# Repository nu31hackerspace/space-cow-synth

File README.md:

# space-cow-synth
Space Cow Synth

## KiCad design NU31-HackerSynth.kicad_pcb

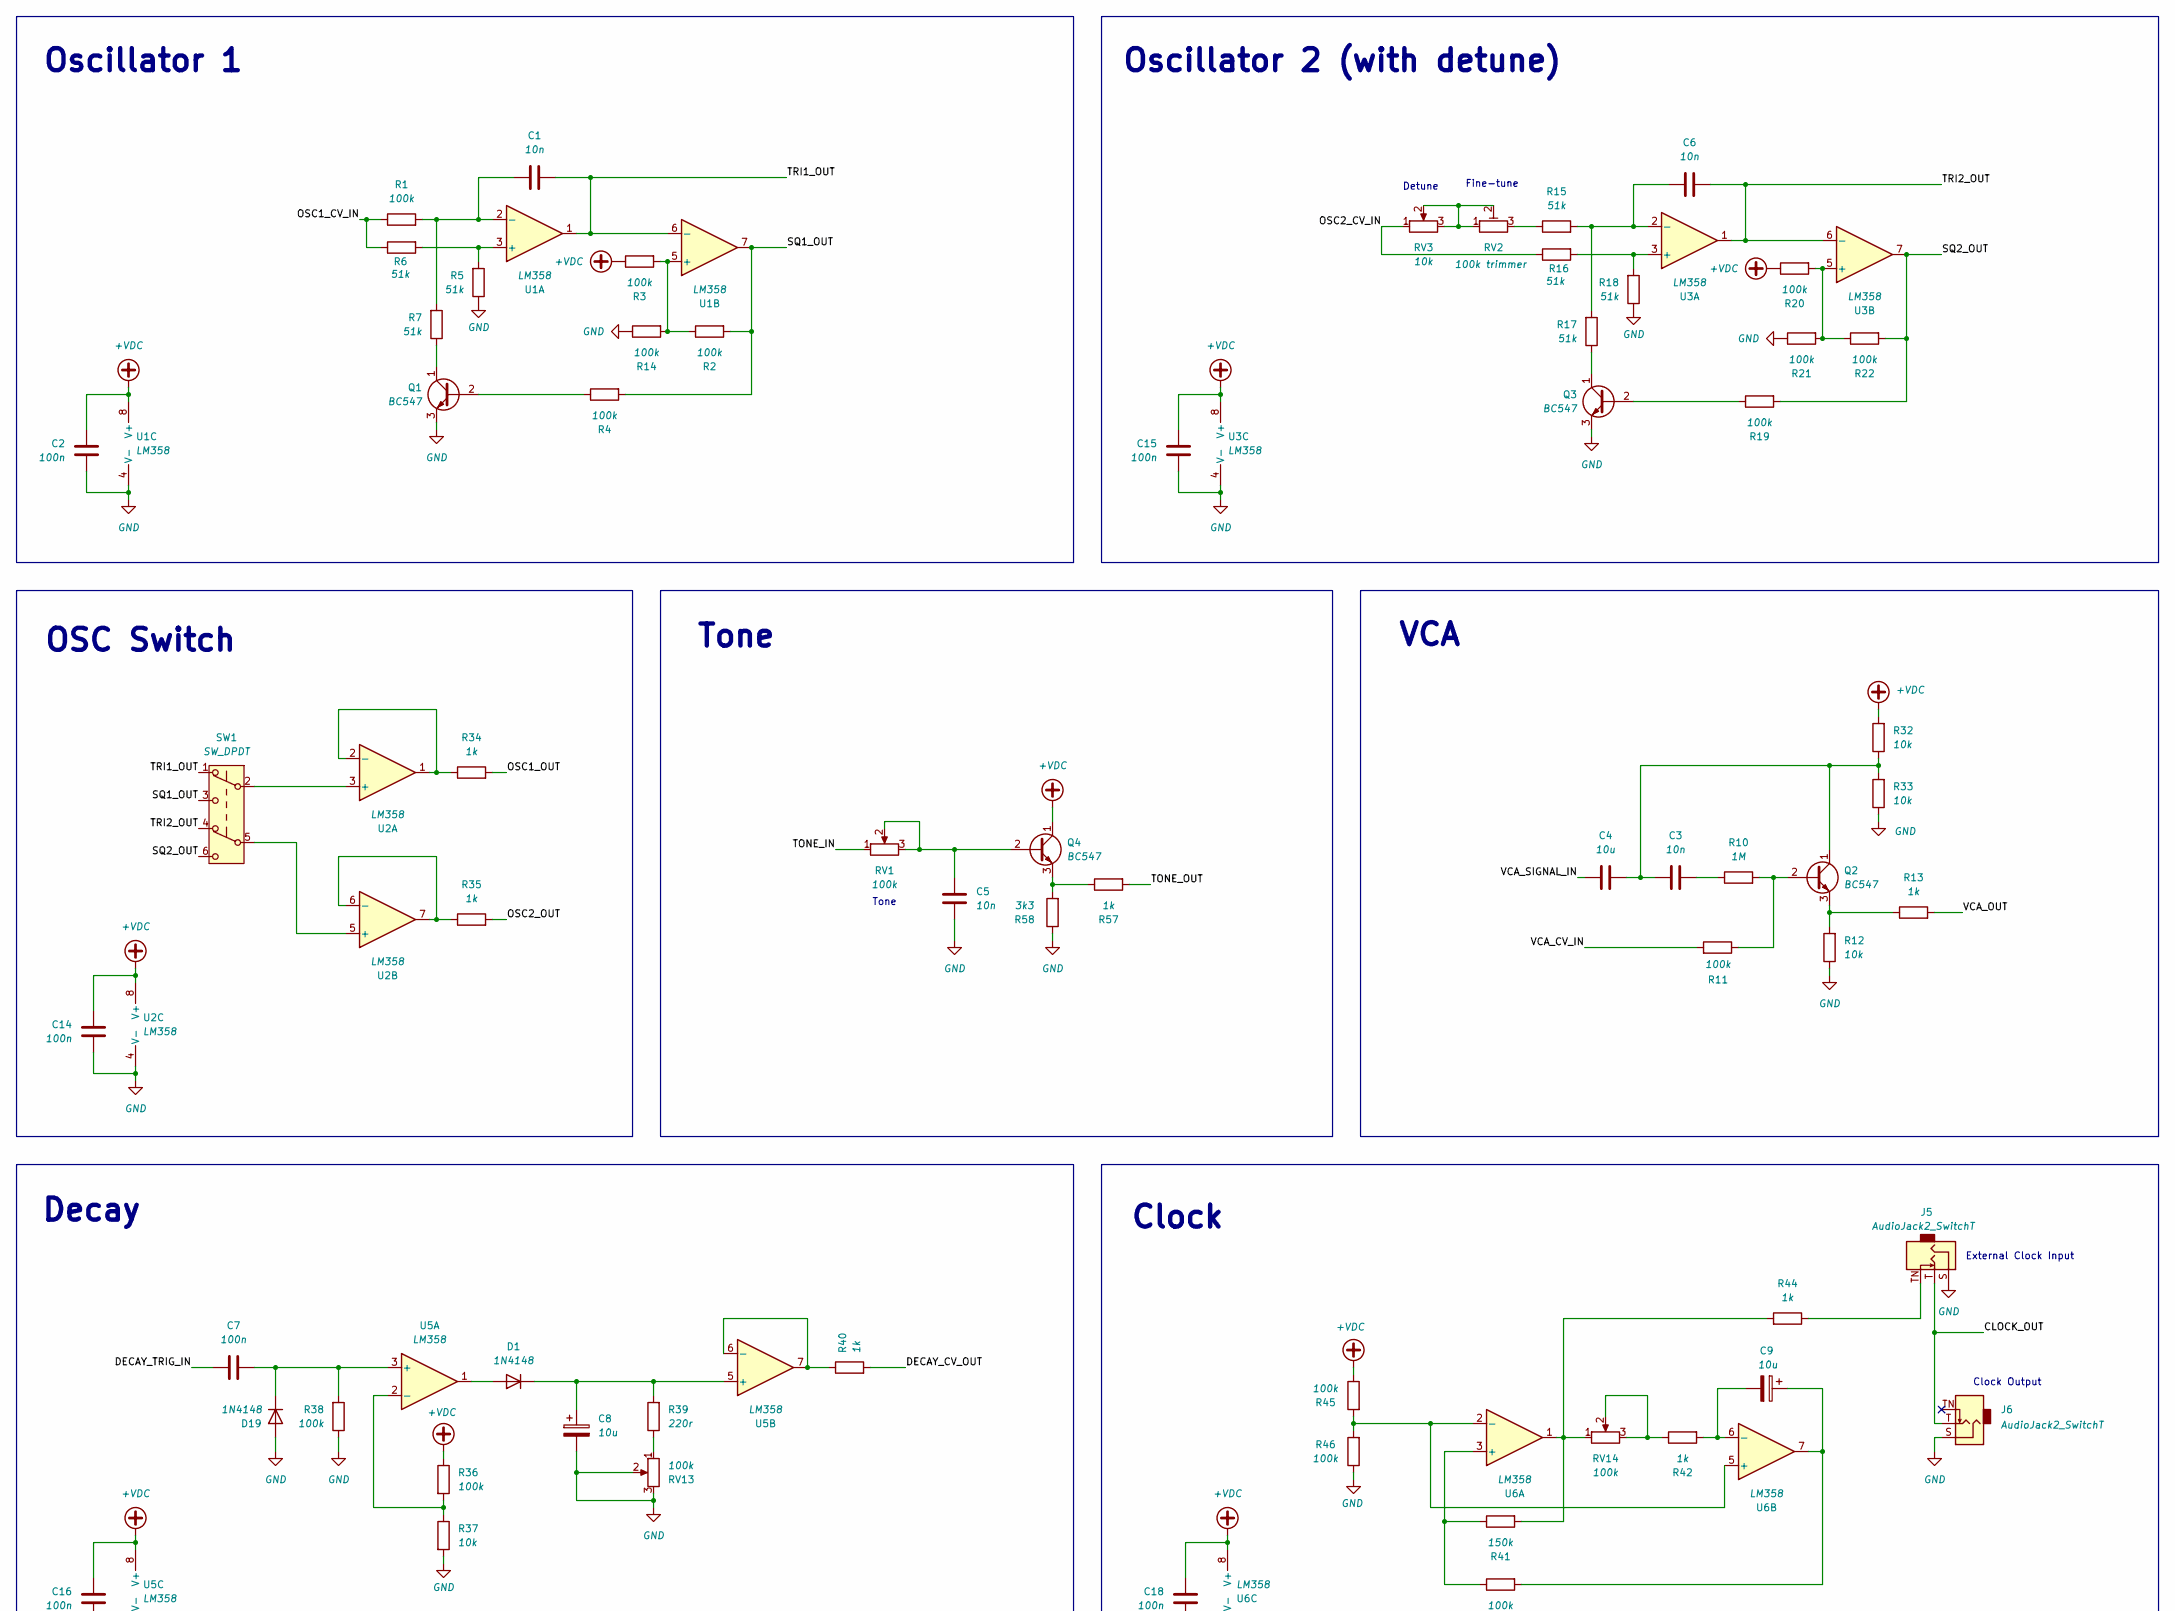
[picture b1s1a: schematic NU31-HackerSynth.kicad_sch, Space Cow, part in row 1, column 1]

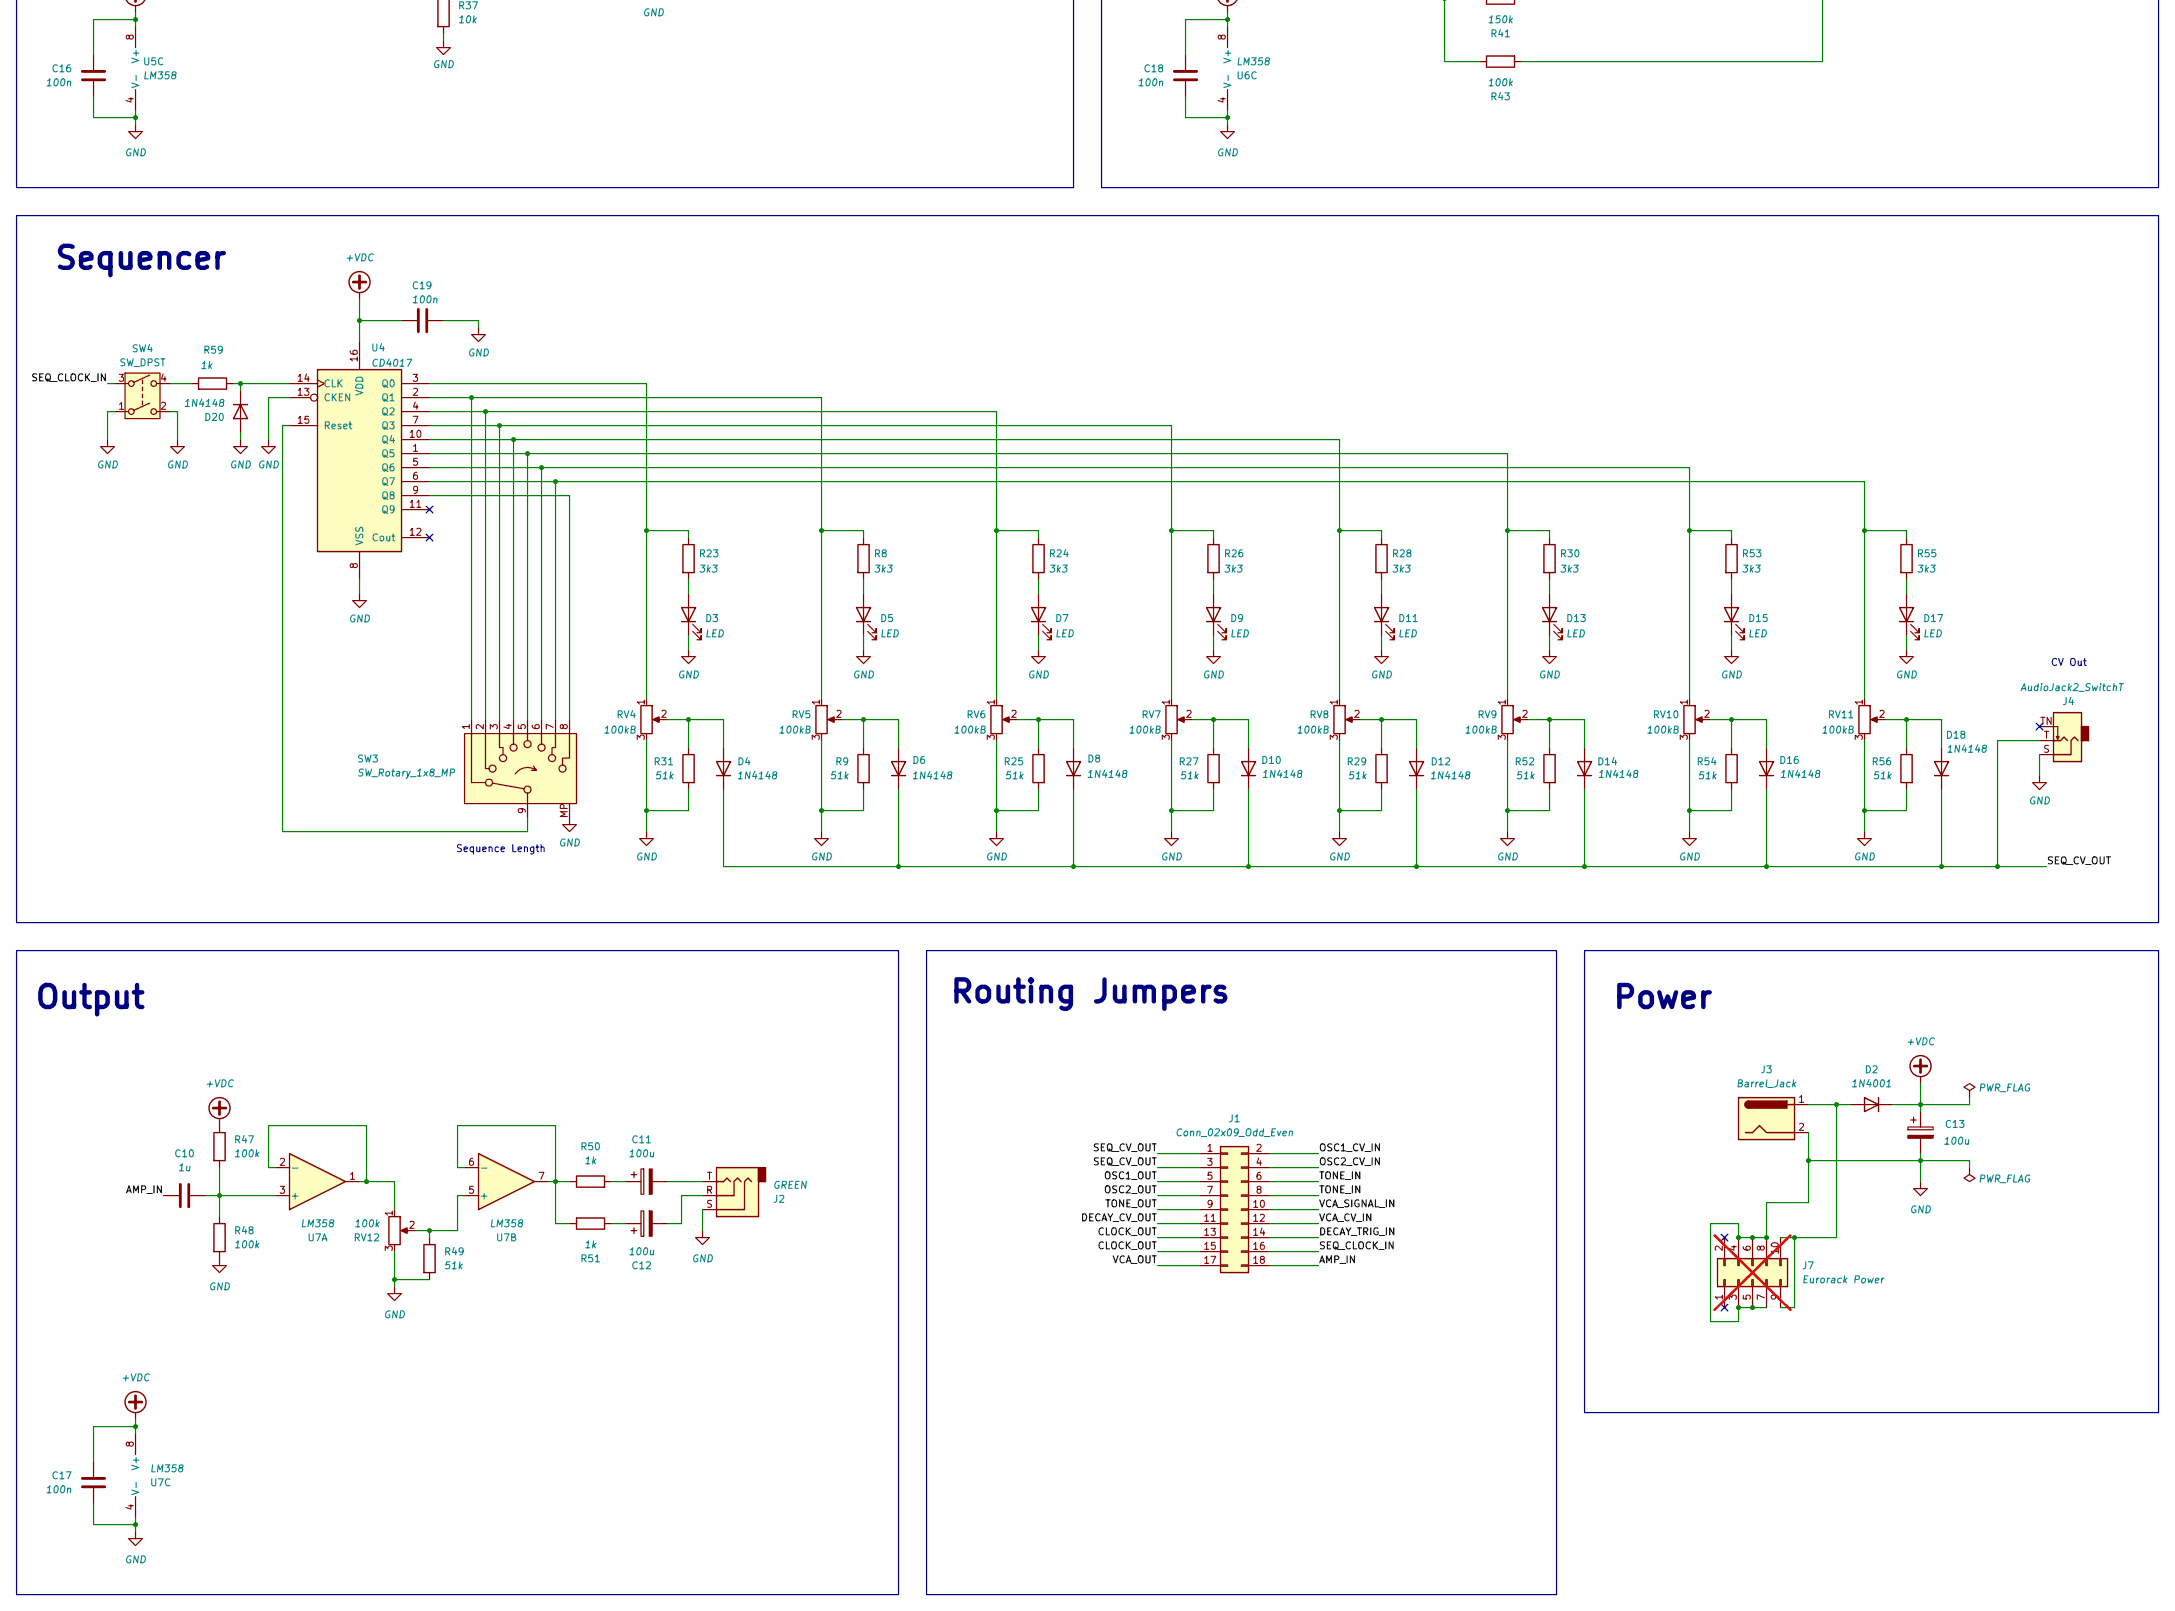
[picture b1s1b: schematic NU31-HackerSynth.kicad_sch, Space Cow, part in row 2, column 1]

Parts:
C1, C3, C5, C6: 10n; C_Disc_D5.1mm_W3.2mm_P5.00mm
C2, C7, C14, C15, C16, C17, C18, C19: 100n; C_Disc_D5.1mm_W3.2mm_P5.00mm
C4: 10u; C_Disc_D5.1mm_W3.2mm_P5.00mm
C8, C9: 10u; CP_Radial_D5.0mm_P2.50mm
C10: 1u; C_Disc_D5.1mm_W3.2mm_P5.00mm
C11, C12, C13: 100u; CP_Radial_D5.0mm_P2.50mm
D1, D4, D6, D8, D10, D12, D14, D16, D18, D19, D20: 1N4148; D_A-405_P7.62mm_Horizontal
D2: 1N4001; D_A-405_P10.16mm_Horizontal
D3, D5, D7, D9, D11, D13, D15, D17: LED; LED_D3.0mm
J1: Conn_02x09_Odd_Even; PinHeader_2x09_P2.54mm_Vertical
J2: GREEN; Jack_3.5mm_QingPu_WQP-PJ366ST_Vertical
J3: Barrel_Jack; BarrelJack_Wuerth_6941xx301002
J4, J5, J6: AudioJack2_SwitchT; Jack_3.5mm_QingPu_WQP-PJ301M-12_Vertical
J7: Eurorack Power; PinSocket_2x05_P2.54mm_Vertical; not fitted
Q1, Q2, Q3, Q4: BC547; TO-92L_Inline_Wide
R1, R2, R3, R4, R11, R14, R19, R20, R21, R22, R36, R38, R43, R45, R46, R47, R48: 100k; R_Axial_DIN0207_L6.3mm_D2.5mm_P10.16mm_Horizontal
R5, R6, R7, R9, R15, R16, R17, R18, R25, R27, R29, R31, R49, R52, R54, R56: 51k; R_Axial_DIN0207_L6.3mm_D2.5mm_P10.16mm_Horizontal
R8, R23, R24, R26, R28, R30, R53, R55, R58: 3k3; R_Axial_DIN0207_L6.3mm_D2.5mm_P10.16mm_Horizontal
R10: 1M; R_Axial_DIN0207_L6.3mm_D2.5mm_P10.16mm_Horizontal
R12, R32, R33, R37: 10k; R_Axial_DIN0207_L6.3mm_D2.5mm_P10.16mm_Horizontal
R13, R34, R35, R40, R42, R44, R50, R51, R57, R59: 1k; R_Axial_DIN0207_L6.3mm_D2.5mm_P10.16mm_Horizontal
R39: 220r; R_Axial_DIN0207_L6.3mm_D2.5mm_P10.16mm_Horizontal
R41: 150k; R_Axial_DIN0207_L6.3mm_D2.5mm_P10.16mm_Horizontal
RV1, RV12, RV13, RV14: 100k; Potentiometer_Alpha_RD901F-40-00D_Single_Vertical
RV2: 100k trimmer; Potentiometer_Bourns_3299P_Horizontal
RV3: 10k; Potentiometer_Alpha_RD901F-40-00D_Single_Vertical
RV4, RV5, RV6, RV7, RV8, RV9, RV10, RV11: 100kB; 40mm Fader Potentiometer (double)
SW1: SW_DPDT; DPDT-subminiature-toggle
SW3: SW_Rotary_1x8_MP; 8-way Rotary Switch
SW4: SW_DPST; 8x8_DPDT_Push_Button
U1, U2, U3, U5, U6, U7: LM358; DIP-8_W7.62mm_Socket
U4: CD4017; DIP-16_W7.62mm_Socket

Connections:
+VDC: C2.1, C13.1, C14.1, C15.1, C16.1, C17.1, C18.1, C19.2, D2.1 (K), Q4.1 (C), R3.1, R20.1, R32.2, R36.1, R45.1, R47.1, U1.8 (V+), U2.8 (V+), U3.8 (V+), U4.16 (VDD), U5.8 (V+), U6.8 (V+), U7.8 (V+)
/AMP_IN: C10.1, J1.18
/CLOCK_OUT: J1.13, J1.15, J5.T, J6.T
/DECAY_CV_OUT: J1.11, R40.2
/DECAY_TRIG_IN: C7.1, J1.14
/OSC1_CV_IN: J1.2, R1.1, R6.1
/OSC1_OUT: J1.5, R34.2
/OSC2_CV_IN: J1.4, R16.1, RV3.1
/OSC2_OUT: J1.7, R35.2
/SEQ_CLOCK_IN: J1.16, SW4.3
/SEQ_CV_OUT: D4.1 (K), D6.1 (K), D8.1 (K), D10.1 (K), D12.1 (K), D14.1 (K), D16.1 (K), D18.1 (K), J1.1, J1.3, J4.T
/SQ1_OUT: R2.2, R4.2, SW1.3 (C), U1.7
/SQ2_OUT: R19.2, R22.2, SW1.6 (C), U3.7
/TONE_IN: J1.6, J1.8, RV1.1
/TONE_OUT: J1.9, R57.2
/TRI1_OUT: C1.2, SW1.1 (A), U1.1, U1.6 (-)
/TRI2_OUT: C6.2, SW1.4 (A), U3.1, U3.6 (-)
/VCA_CV_IN: J1.12, R11.2
/VCA_OUT: J1.17, R13.2
/VCA_SIGNAL_IN: C4.1, J1.10
GND: C2.2, C5.2, C8.2, C13.2, C14.2, C15.2, C16.2, C17.2, C18.2, C19.1, D3.1 (K), D5.1 (K), D7.1 (K), D9.1 (K), D11.1 (K), D13.1 (K), D15.1 (K), D17.1 (K), D19.2 (A), D20.2 (A), J2.S, J3.2, J4.S, J5.S, J6.S, J7.3, J7.4, J7.5, J7.6, J7.7, J7.8, Q1.3 (E), Q3.3 (E), R5.1, R9.2, R12.1, R14.1, R18.1, R21.1, R25.2, R27.2, R29.2, R31.2, R33.1, R37.2, R38.1, R46.1, R48.2, R49.2, R52.2, R54.2, R56.2, R58.1, RV4.3, RV5.3, RV6.3, RV7.3, RV8.3, RV9.3, RV10.3, RV11.3, RV12.3, RV13.2, RV13.3, SW3.MP, SW4.1, SW4.2, U1.4 (V-), U2.4 (V-), U3.4 (V-), U4.8 (VSS), U4.13 (CKEN), U5.4 (V-), U6.4 (V-), U7.4 (V-)
unnamed: C3.2, R10.1
unnamed: C9.1, R43.2, U6.7
unnamed: C11.1, R50.2
unnamed: C11.2, J2.T
unnamed: C12.1, R51.1
unnamed: C12.2, J2.R
unnamed: D1.2 (A), U5.1
unnamed: C8.1, D1.1 (K), R39.2, U5.5 (+)
unnamed: D2.2 (A), J3.1, J7.9, J7.10
unnamed: D3.2 (A), R23.2
unnamed: D4.2 (A), R31.1, RV4.2
unnamed: D5.2 (A), R8.2
unnamed: D6.2 (A), R9.1, RV5.2
unnamed: D7.2 (A), R24.2
unnamed: D8.2 (A), R25.1, RV6.2
unnamed: D9.2 (A), R26.2
unnamed: D10.2 (A), R27.1, RV7.2
unnamed: D11.2 (A), R28.2
unnamed: D12.2 (A), R29.1, RV8.2
unnamed: D13.2 (A), R30.2
unnamed: D14.2 (A), R52.1, RV9.2
unnamed: D15.2 (A), R53.2
unnamed: D16.2 (A), R54.1, RV10.2
unnamed: D17.2 (A), R55.2
unnamed: D18.2 (A), R56.1, RV11.2
unnamed: C7.2, D19.1 (K), R38.2, U5.3 (+)
unnamed: D20.1 (K), R59.1, U4.14 (CLK)
unnamed: J5.TN, R44.1
unnamed: Q1.2 (B), R4.1
unnamed: Q1.1 (C), R7.1
unnamed: Q2.2 (B), R10.2, R11.1
unnamed: C3.1, C4.2, Q2.1 (C), R32.1, R33.2
unnamed: Q2.3 (E), R12.2, R13.1
unnamed: Q3.2 (B), R19.1
unnamed: Q3.1 (C), R17.1
unnamed: C5.1, Q4.2 (B), RV1.2, RV1.3
unnamed: Q4.3 (E), R57.1, R58.2
unnamed: R15.1, RV2.3
unnamed: R39.1, RV13.1
unnamed: R41.2, R44.2, RV14.1, U6.1
unnamed: R42.1, RV14.2, RV14.3
unnamed: R59.2, SW4.4
unnamed: RV2.1, RV2.2, RV3.2, RV3.3
unnamed: R5.2, R6.2, U1.3 (+)
unnamed: C1.1, R1.2, R7.2, U1.2 (-)
unnamed: R2.1, R3.2, R14.2, U1.5 (+)
unnamed: SW1.2 (B), U2.3 (+)
unnamed: R34.1, U2.1, U2.2 (-)
unnamed: SW1.5 (B), U2.5 (+)
unnamed: R35.1, U2.6 (-), U2.7
unnamed: R16.2, R18.2, U3.3 (+)
unnamed: C6.1, R15.2, R17.2, U3.2 (-)
unnamed: R20.2, R21.2, R22.1, U3.5 (+)
unnamed: R23.1, RV4.1, U4.3 (Q0)
unnamed: R8.1, RV5.1, SW3.1, U4.2 (Q1)
unnamed: R24.1, RV6.1, SW3.2, U4.4 (Q2)
unnamed: R26.1, RV7.1, SW3.3, U4.7 (Q3)
unnamed: R28.1, RV8.1, SW3.4, U4.10 (Q4)
unnamed: R30.1, RV9.1, SW3.5, U4.1 (Q5)
unnamed: R53.1, RV10.1, SW3.6, U4.5 (Q6)
unnamed: R55.1, RV11.1, SW3.7, U4.6 (Q7)
unnamed: SW3.8, U4.9 (Q8)
unnamed: SW3.9, U4.15 (Reset)
unnamed: R36.2, R37.1, U5.2 (-)
unnamed: R40.1, U5.6 (-), U5.7
unnamed: R41.1, R43.1, U6.3 (+)
unnamed: R45.2, R46.2, U6.2 (-), U6.5 (+)
unnamed: C9.2, R42.2, U6.6 (-)
unnamed: C10.2, R47.2, R48.1, U7.3 (+)
unnamed: RV12.1, U7.1, U7.2 (-)
unnamed: R49.1, RV12.2, U7.5 (+)
unnamed: R50.1, R51.2, U7.6 (-), U7.7

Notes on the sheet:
Sequencer
VCA
Oscillator 2 (with detune)
CV Out
Fine-tune
Power
Clock Output
Sequence Length
Tone
Routing Jumpers
Decay
External Clock Input
Output
Oscillator 1
OSC Switch
Detune
Clock

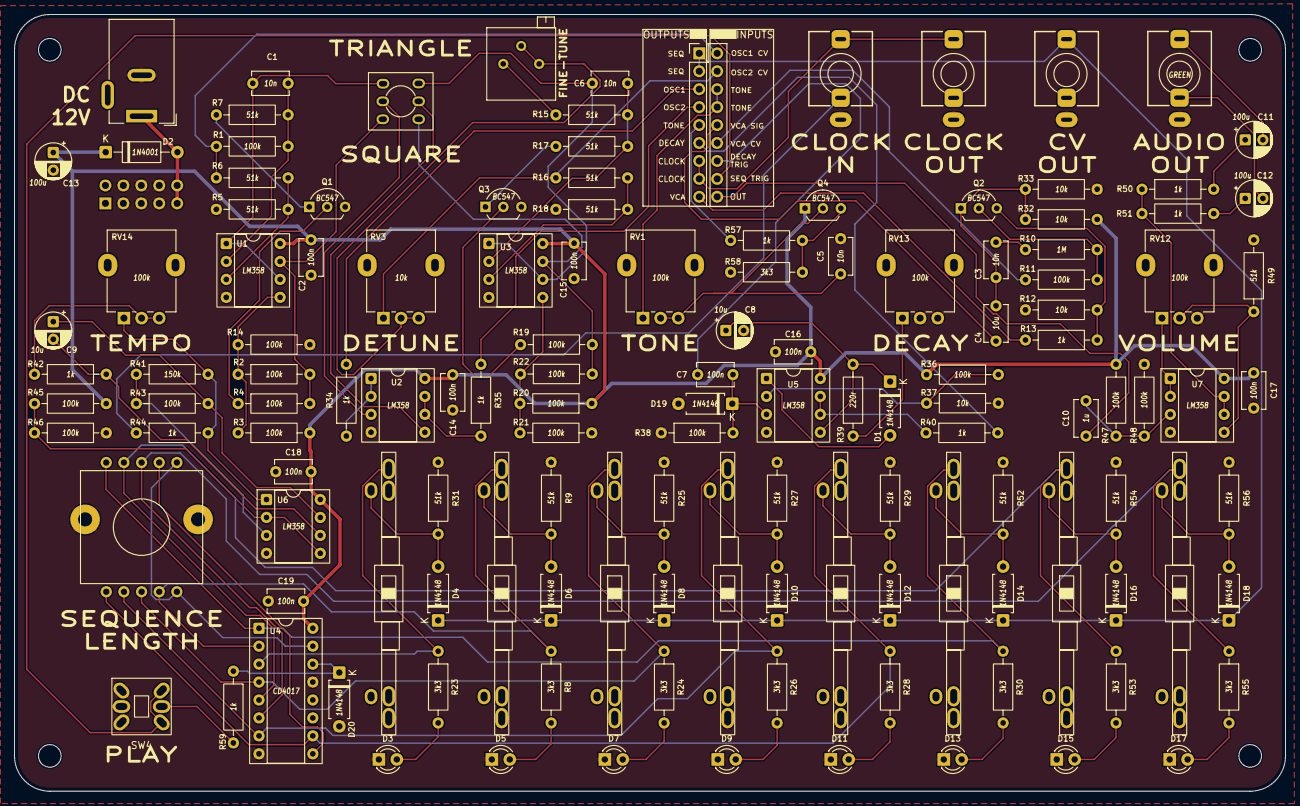
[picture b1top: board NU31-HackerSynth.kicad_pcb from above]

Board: 2 copper layers, 180.0 x 110.0 mm, 133 parts (1 on the bottom side), 93 nets.

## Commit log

2025-08-31 Updated schematics layout, added clock input and output jacks and CV output jack, changed sequence length jumper pins from 7x2 to 8x2 (2 pins unconnected, just to keep the jumper)
2025-08-31 Grounded CKEN and CLK switch, switched diodes in sequencer to 1N4148
2025-08-31 Added buffer to mixer output, connected last step reset jumper pins
2025-09-04 added schematics PDF
2025-09-04 Added eurorack power connector, assigned the footprints and made a (very) draft layout of the board
2025-09-04 Replaced sequence length jumper pins with 8-position switch
2025-09-04 updated PDF schematic
2025-09-04 Added diode to filter out negatvie voltages in decay circuit input
2025-09-06 Updated and separated OSC type switch and tone control into separate blocks
2025-09-19 Added negative voltage protection for sequencer clock input, added footprints for faders and rotaryswitch
2025-09-20 added decoupling cap for CD4017, replaced all routing jumpers with one pin header
2025-09-25 Changed slider-switches to push-button and toggle switch, renamed mixer pins to tone
2025-09-26 Board layout is ready. Also fixed some wrong polarity issues in the schematics
2025-09-26 Updated pdf schematics
2025-09-26 Changed VCC trace width to 0.5mm, changed clearence to 0.2
2025-09-26 Updated OSC shape switch footprint, optimized routing for decoupling capacitors and ground plane
2025-09-26 tidied up capacitor values on silkscreen
2025-09-28 removed stray part of the trace
2025-10-19 fixed clock switch pinout and footprint
2025-11-12 Fine-tuned the value, fixed power polarity in the schematics
2025-11-21 updated fader footprint, fixed DC barrel polarity in the layout
